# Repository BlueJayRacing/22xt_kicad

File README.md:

# 22xt_kicad, JHU Blue Jay Racing Repository
This is the KiCad Repository for the JHU 22XT DAQ Sub-team.

## Installation and User Guide
GitHub & KiCad Guide: https://docs.google.com/document/d/1nFm-e38JEY4i58-0UFxqdLA5TKqWCrV3EDKR8jGpRfA/edit?usp=sharing 

As a summary, you should be using **KiCad Version 9.0**. All project will be modular, and you should be storing all your step files, symbols, & footprints within the created folders.

Schematic settings & layout settings are described in the guide, as well as component derating.

## Branch Guide
You should be working on a new branch for each revision of your board. It is only when your board gets ordered on JLC that it should be merged with the main branch.

<ins>Branch naming structure:</ins> [0X]-[boardname]

Example:
> 01-main_board

<ins>How-To Create a Branch:</ins>

```
git checkout -b [your_branch] main
git push -u origin [your_branch]
```

## KiCad Project Name

Create your KiCad project on YOUR branch, within your current project folder.

<ins>Project filepath:</ins> [your_folder]/[boardname]_v[X]

Example Path:
> 01-main_board/main_board_v1

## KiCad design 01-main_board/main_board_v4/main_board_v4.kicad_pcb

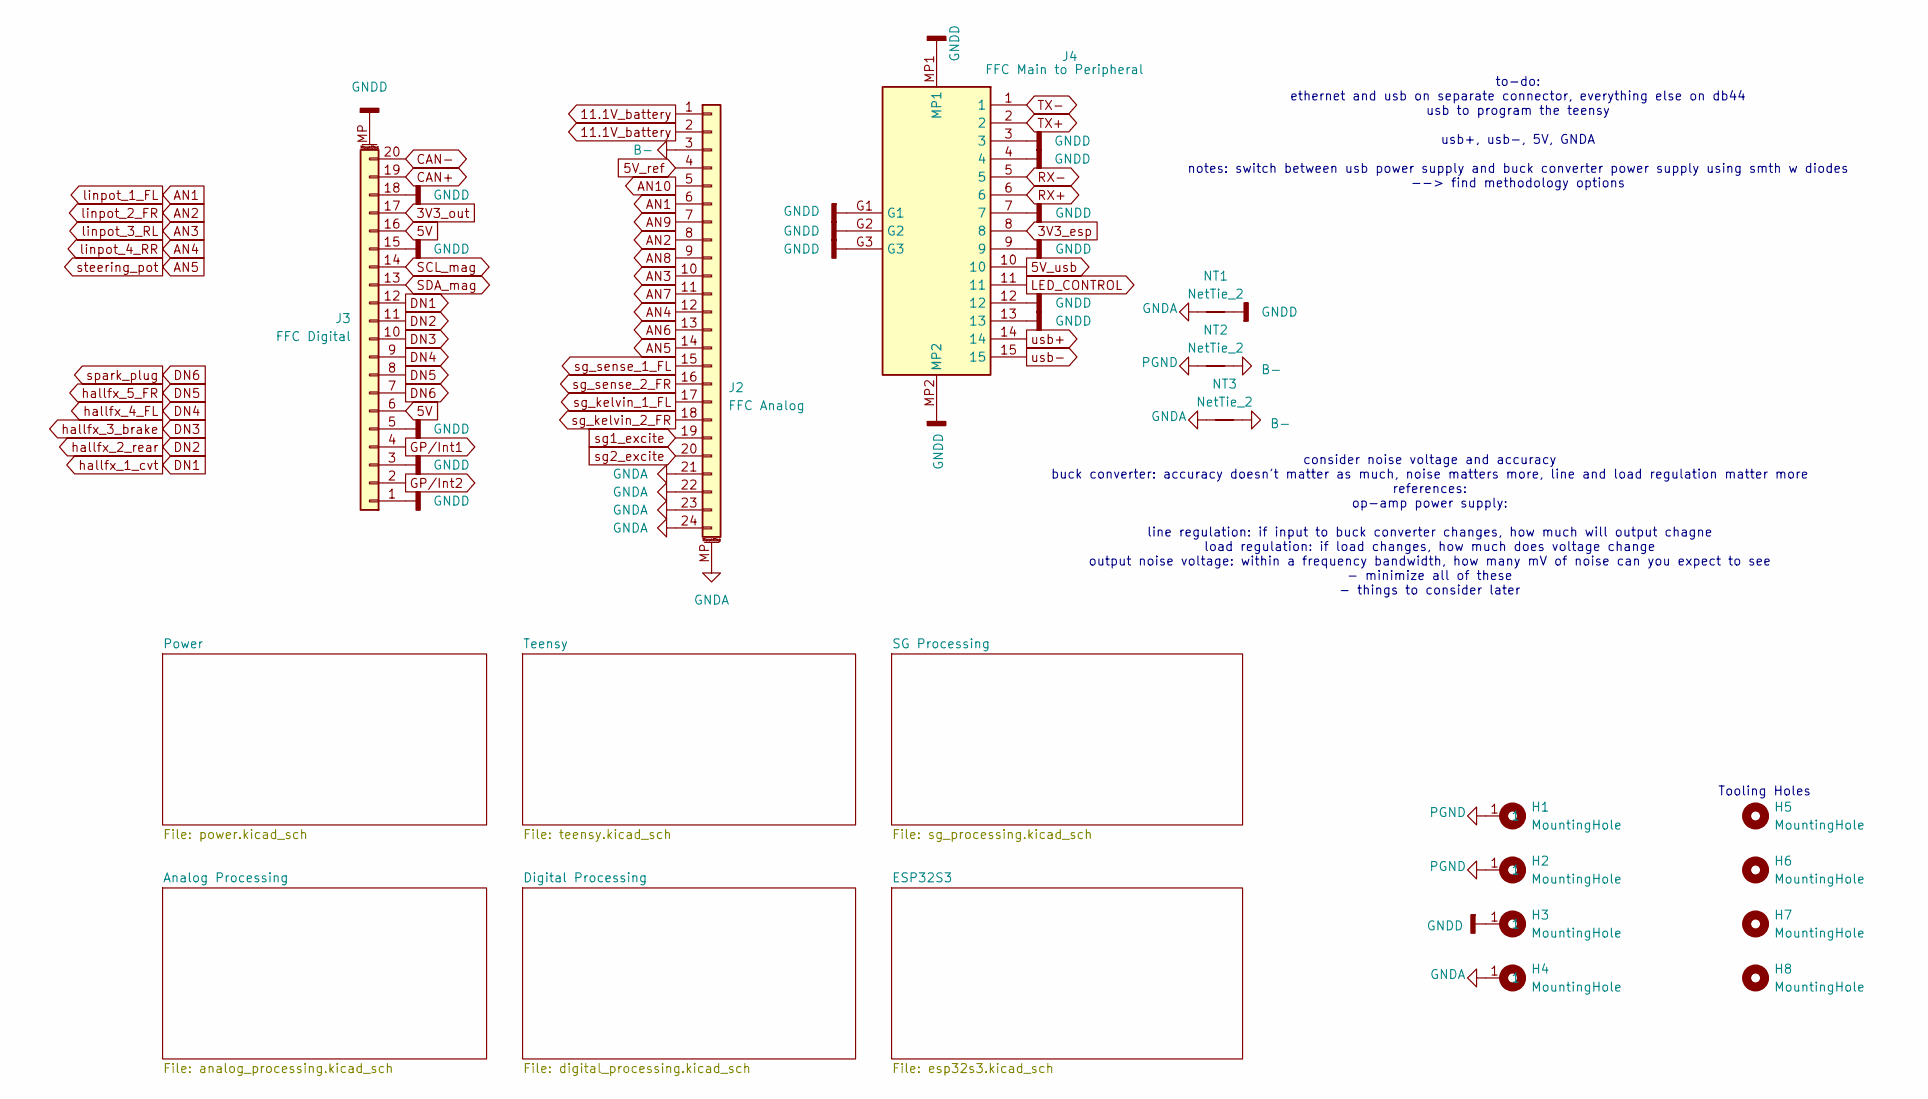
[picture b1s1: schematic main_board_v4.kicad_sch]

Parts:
H1, H2, H3, H4: MountingHole; MountingHole_2.5mm_Pad
H5, H6, H7, H8: MountingHole; ToolingHole_1.152mm
J2: FFC Analog; TE_2-84952-4_1x24-1MP_P1.0mm_Horizontal
J3: FFC Digital; TE_2-84952-0_1x20-1MP_P1.0mm_Horizontal
J4: FFC Main to Peripheral; FH4115S05SH05; Mouser Part Number 798-FH4115S05SH05
NT1, NT2, NT3: NetTie_2; NetTie-2_SMD_Pad0.5mm

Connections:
2V5: J2.19, J2.20; also elsewhere on the board
3V3_esp: J4.8; also elsewhere on the board
3V3_out: J3.17; also elsewhere on the board
5V: J3.6, J3.16; also elsewhere on the board
5V_ref: J2.4; also elsewhere on the board
5V_usb: J4.10; also elsewhere on the board
11.1V_battery: J2.1, J2.2; also elsewhere on the board
AN1: J2.6; also elsewhere on the board
AN2: J2.8; also elsewhere on the board
AN3: J2.10; also elsewhere on the board
AN4: J2.12; also elsewhere on the board
AN5: J2.14; also elsewhere on the board
AN6: J2.13; also elsewhere on the board
AN7: J2.11; also elsewhere on the board
AN8: J2.9; also elsewhere on the board
AN9: J2.7; also elsewhere on the board
AN10: J2.5; also elsewhere on the board
B-: J2.3, NT2.2, NT3.2
CAN+: J3.19; also elsewhere on the board
CAN-: J3.20; also elsewhere on the board
DN1: J3.12; also elsewhere on the board
DN2: J3.11; also elsewhere on the board
DN3: J3.10; also elsewhere on the board
DN4: J3.9; also elsewhere on the board
DN5: J3.8; also elsewhere on the board
DN6: J3.7; also elsewhere on the board
GNDA: H4.1, J2.21, J2.22, J2.23, J2.24, J2.MP (MountPin), NT1.1, NT3.1; also elsewhere on the board
GNDD: H3.1, J3.1, J3.3, J3.5, J3.15, J3.18, J3.MP (MountPin), J4.3, J4.4, J4.7, J4.9, J4.12, J4.13, J4.G1, J4.G2, J4.G3, J4.MP1, J4.MP2, NT1.2; also elsewhere on the board
GP/Int1: J3.4; also elsewhere on the board
GP/Int2: J3.2; also elsewhere on the board
LED_CONTROL: J4.11; also elsewhere on the board
PGND: H1.1, H2.1, NT2.1; also elsewhere on the board
RX+: J4.6; also elsewhere on the board
RX-: J4.5; also elsewhere on the board
SCL_mag: J3.14; also elsewhere on the board
SDA_mag: J3.13; also elsewhere on the board
TX+: J4.2; also elsewhere on the board
TX-: J4.1; also elsewhere on the board
sg1+: J2.17; also elsewhere on the board
sg2+: J2.18; also elsewhere on the board
sg_sense_1_FL: J2.15; also elsewhere on the board
sg_sense_2_FR: J2.16; also elsewhere on the board
usb+: J4.14; also elsewhere on the board
usb-: J4.15; also elsewhere on the board

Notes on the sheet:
consider noise voltage and accuracy buck converter: accuracy doesn't matter as much, noise matters more, line and load regulation matter more references: op-amp power supply: line regulation: if input to buck converter changes, how much will output chagne load regulation: if load changes, how much 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
to-do: ethernet and usb on separate connector, everything else on db44 usb to program the teensy usb+, usb-, 5V, GNDA notes: switch between usb power supply and buck converter power supply using smth w diodes --> find methodology options
Tooling Holes

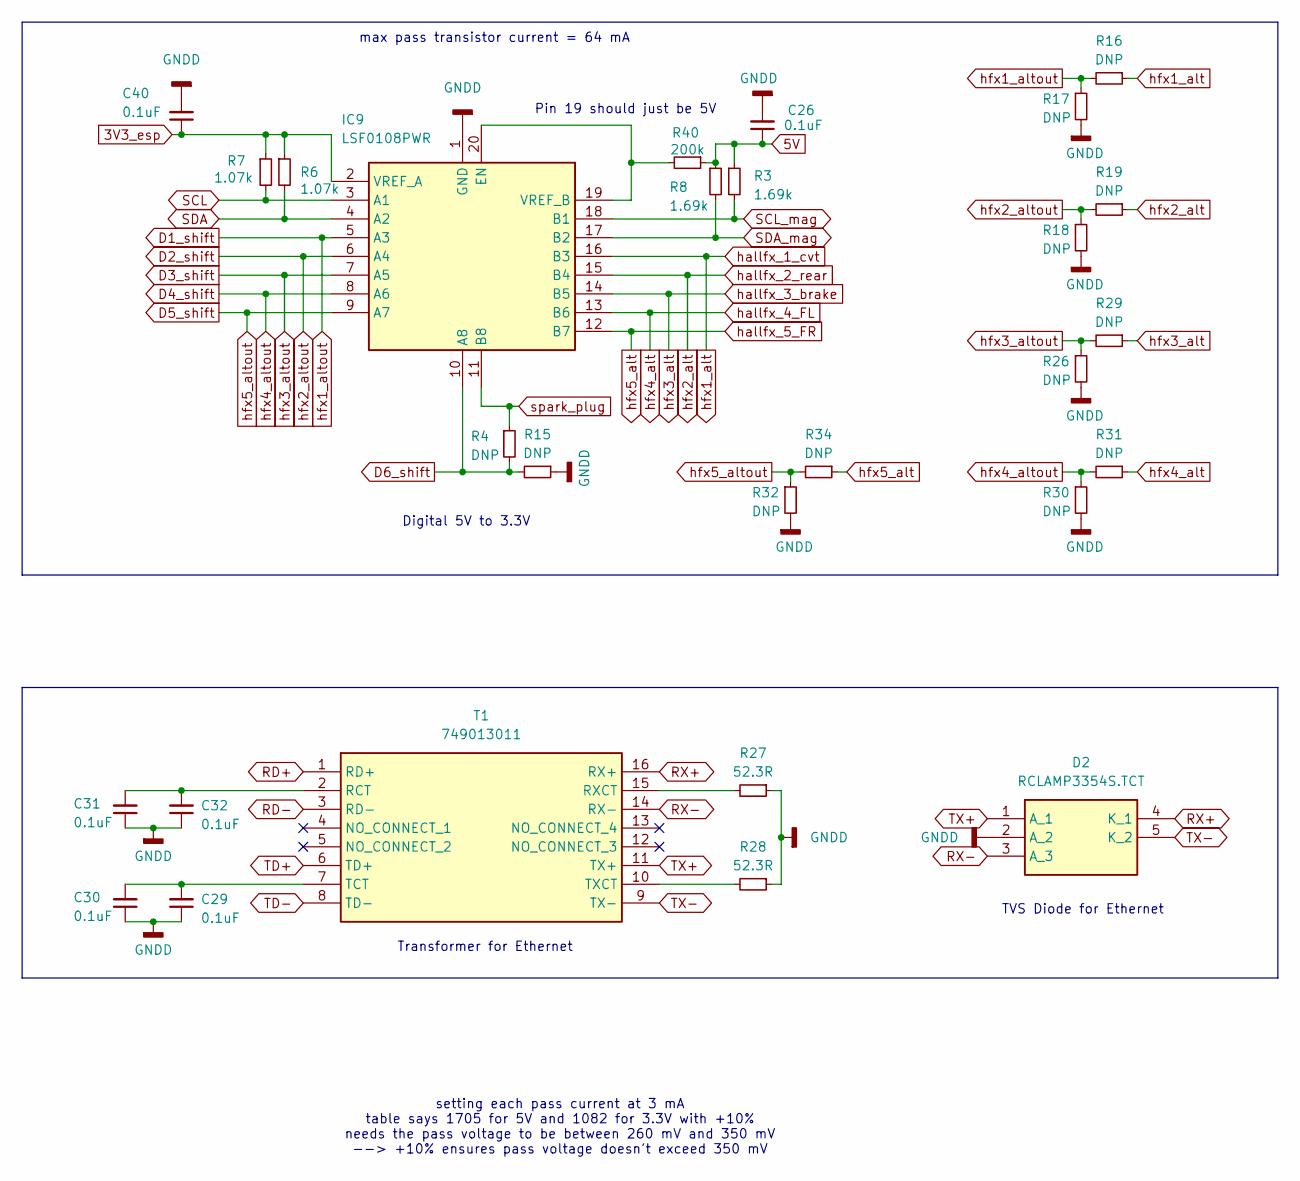
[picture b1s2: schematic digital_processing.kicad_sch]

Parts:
C26, C29, C30, C31, C32, C40: 0.1uF; C_0402_1005Metric
D2: RCLAMP3354S.TCT; SOT-23-5; Mouser Part Number 947-RCLAMP3354S.TCT
IC9: LSF0108PWR; SOP65P640X120-20N; Mouser Part Number 595-LSF0108RKSR
R3, R8: 1.69k; R_0402_1005Metric
R4, R15, R16, R17, R18, R19, R26, R29, R30, R31, R32, R34: DNP; R_0402_1005Metric
R6, R7: 1.07k; R_0402_1005Metric
R27, R28: 52.3R; R_0402_1005Metric
R40: 200k; R_0402_1005Metric
T1: 749013011; Mouser Part Number 710-749013011

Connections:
3V3_esp: C40.1, IC9.2 (VREF_A), R6.1, R7.1; also elsewhere on the board
5V: C26.1, R3.1, R8.1, R40.1; also elsewhere on the board
D1_shift: IC9.5 (A3), R16.2, R17.1; also elsewhere on the board
D2_shift: IC9.6 (A4), R18.1, R19.2; also elsewhere on the board
D3_shift: IC9.7 (A5), R26.1, R29.2; also elsewhere on the board
D4_shift: IC9.8 (A6), R30.1, R31.2; also elsewhere on the board
D5_shift: IC9.9 (A7), R32.1, R34.2; also elsewhere on the board
D6_shift: IC9.10 (A8), R4.2, R15.2; also elsewhere on the board
DN1: IC9.16 (B3), R16.1; also elsewhere on the board
DN2: IC9.15 (B4), R19.1; also elsewhere on the board
DN3: IC9.14 (B5), R29.1; also elsewhere on the board
DN4: IC9.13 (B6), R31.1; also elsewhere on the board
DN5: IC9.12 (B7), R34.1; also elsewhere on the board
DN6: IC9.11 (B8), R4.1; also elsewhere on the board
GNDD: C26.2, C29.1, C30.1, C31.1, C32.1, C40.2, D2.2 (A_2), IC9.1 (GND), R15.1, R17.2, R18.2, R26.2, R27.1, R28.1, R30.2, R32.2; also elsewhere on the board
unnamed: IC9.19 (VREF_B), IC9.20 (EN), R40.2
unnamed: C31.2, C32.2, T1.2 (RCT)
unnamed: R27.2, T1.15 (RXCT)
unnamed: C29.2, C30.2, T1.7 (TCT)
unnamed: R28.2, T1.10 (TXCT)
RD+: T1.1 (RD+); also elsewhere on the board
RD-: T1.3 (RD-); also elsewhere on the board
RX+: D2.4 (K_1), T1.16 (RX+); also elsewhere on the board
RX-: D2.3 (A_3), T1.14 (RX-); also elsewhere on the board
SCL: IC9.3 (A1), R7.2; also elsewhere on the board
SCL_mag: IC9.18 (B1), R3.2; also elsewhere on the board
SDA: IC9.4 (A2), R6.2; also elsewhere on the board
SDA_mag: IC9.17 (B2), R8.2; also elsewhere on the board
TD+: T1.6 (TD+); also elsewhere on the board
TD-: T1.8 (TD-); also elsewhere on the board
TX+: D2.1 (A_1), T1.11 (TX+); also elsewhere on the board
TX-: D2.5 (K_2), T1.9 (TX-); also elsewhere on the board

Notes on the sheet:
Transformer for Ethernet
max pass transistor current = 64 mA
Digital 5V to 3.3V
TVS Diode for Ethernet
setting each pass current at 3 mA table says 1705 for 5V and 1082 for 3.3V with +10% needs the pass voltage to be between 260 mV and 350 mV --> +10% ensures pass voltage doesn't exceed 350 mV
Pin 19 should just be 5V

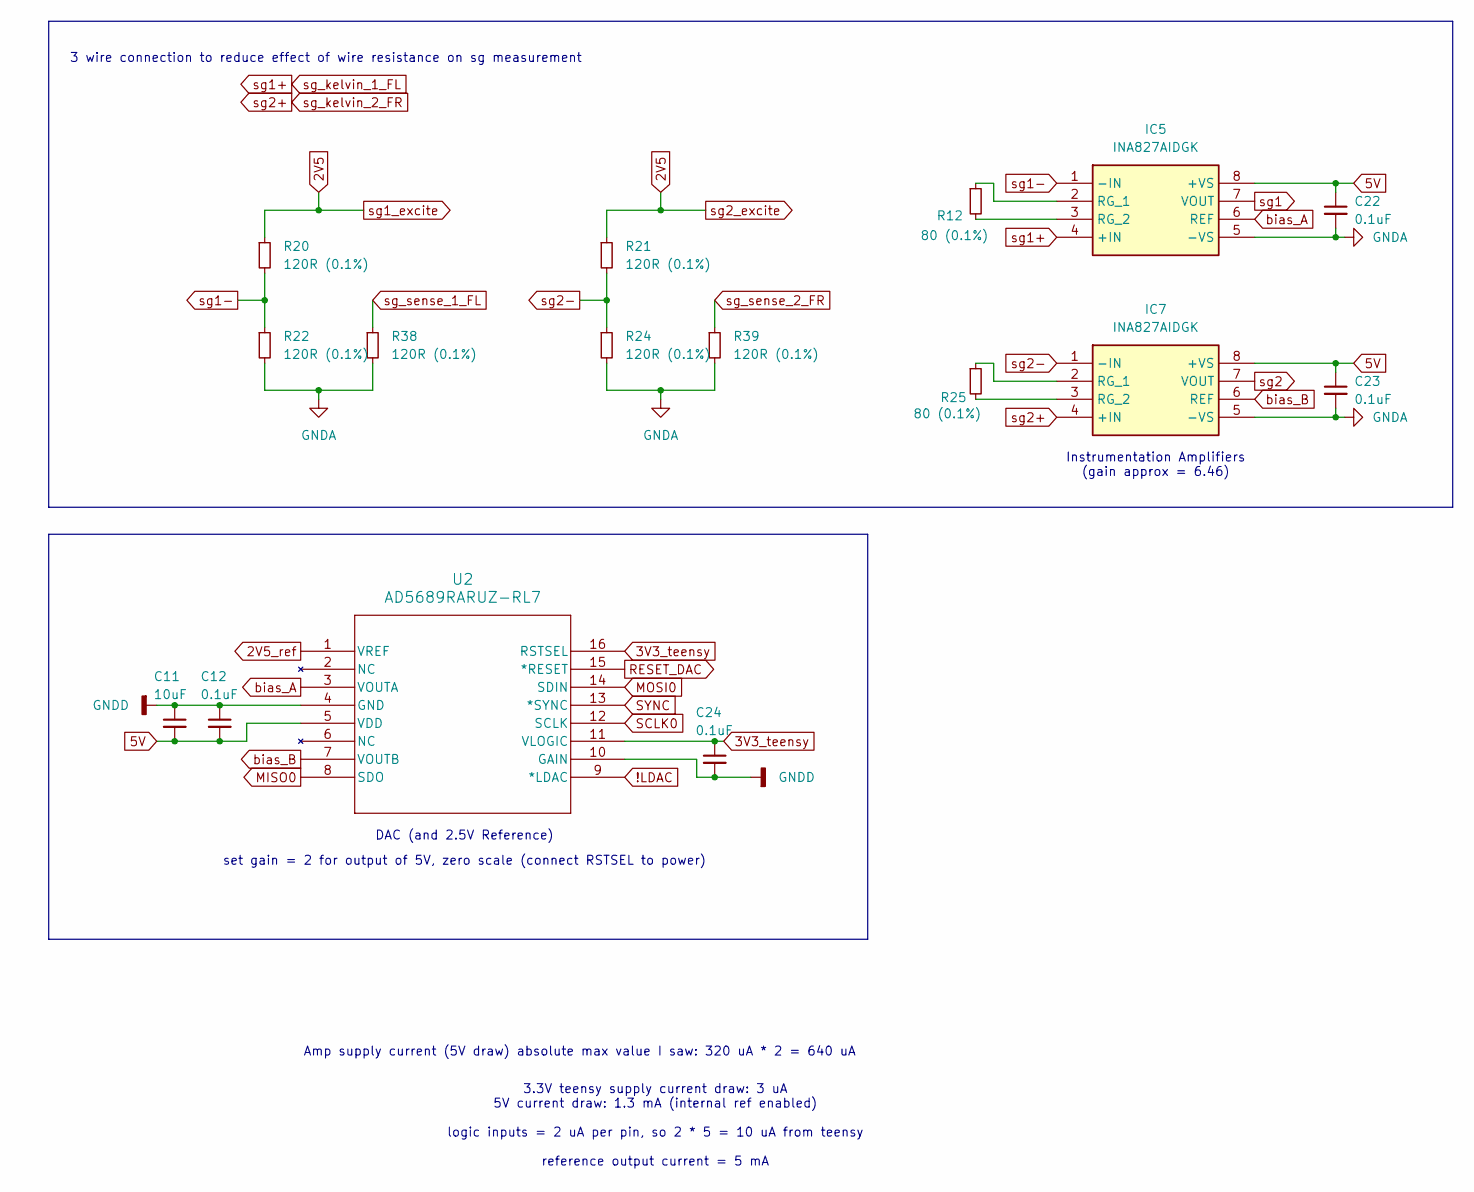
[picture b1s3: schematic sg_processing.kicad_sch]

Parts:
C11: 10uF; C_0603_1608Metric
C12, C22, C23, C24: 0.1uF; C_0402_1005Metric
IC5, IC7: INA827AIDGK; SOP65P490X110-8N; Mouser Part Number 595-INA827AIDGK
R12, R25: 80 (0.1%); R_0402_1005Metric
R20, R21, R22, R24, R38, R39: 120R (0.1%); R_0402_1005Metric
U2: AD5689RARUZ-RL7; RU_16_ADI

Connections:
2V5: R20.1, R21.1; also elsewhere on the board
2V5_ref: U2.1 (VREF); also elsewhere on the board
3V3_teensy: C24.1, U2.11 (VLOGIC), U2.16 (RSTSEL); also elsewhere on the board
5V: C11.2, C12.2, C22.1, C23.1, IC5.8 (+VS), IC7.8 (+VS), U2.5 (VDD); also elsewhere on the board
!LDAC: U2.9 (*LDAC); also elsewhere on the board
GNDA: C22.2, C23.2, IC5.5 (-VS), IC7.5 (-VS), R22.2, R24.2, R38.2, R39.2; also elsewhere on the board
GNDD: C11.1, C12.1, C24.2, U2.4 (GND), U2.10 (GAIN); also elsewhere on the board
MISO0: U2.8 (SDO); also elsewhere on the board
MOSI0: U2.14 (SDIN); also elsewhere on the board
unnamed: IC5.2 (RG_1), R12.1
unnamed: IC5.3 (RG_2), R12.2
unnamed: IC7.2 (RG_1), R25.1
unnamed: IC7.3 (RG_2), R25.2
RESET_DAC: U2.15 (*RESET); also elsewhere on the board
SCLK0: U2.12 (SCLK); also elsewhere on the board
SYNC: U2.13 (*SYNC); also elsewhere on the board
bias_A: IC5.6 (REF), U2.3 (VOUTA)
bias_B: IC7.6 (REF), U2.7 (VOUTB)
sg1: IC5.7 (VOUT); also elsewhere on the board
sg1+: IC5.4 (+IN); also elsewhere on the board
sg1-: IC5.1 (-IN), R20.2, R22.1
sg2: IC7.7 (VOUT); also elsewhere on the board
sg2+: IC7.4 (+IN); also elsewhere on the board
sg2-: IC7.1 (-IN), R21.2, R24.1
sg_sense_1_FL: R38.1; also elsewhere on the board
sg_sense_2_FR: R39.1; also elsewhere on the board

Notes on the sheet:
DAC (and 2.5V Reference)
Amp supply current (5V draw) absolute max value I saw: 320 uA * 2 = 640 uA
3.3V teensy supply current draw: 3 uA 5V current draw: 1.3 mA (internal ref enabled) logic inputs = 2 uA per pin, so 2 * 5 = 10 uA from teensy reference output current = 5 mA
set gain = 2 for output of 5V, zero scale (connect RSTSEL to power)
Instrumentation Amplifiers (gain approx = 6.46)
3 wire connection to reduce effect of wire resistance on sg measurement

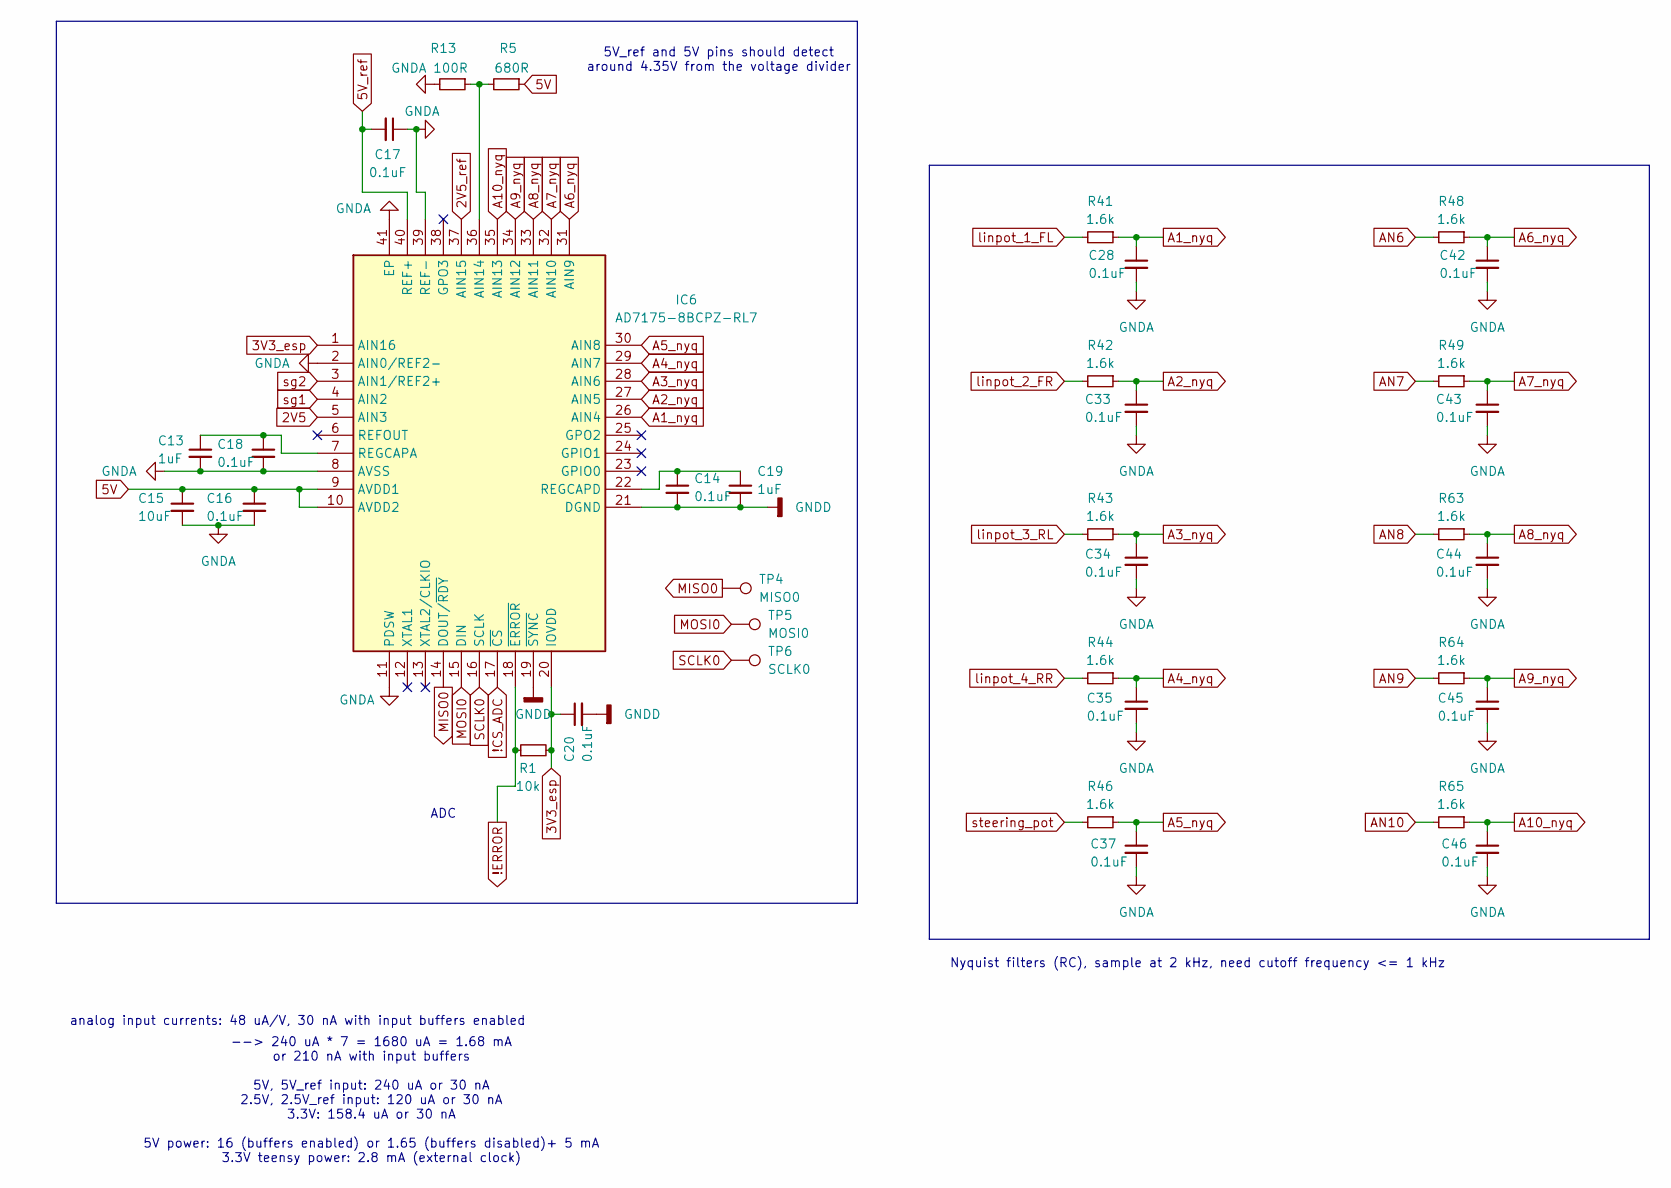
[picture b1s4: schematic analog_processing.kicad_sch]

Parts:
C13, C19: 1uF; C_0402_1005Metric
C14, C16, C17, C18, C20, C28, C33, C34, C35, C37, C42, C43, C44, C45, C46: 0.1uF; C_0402_1005Metric
C15: 10uF; C_0603_1608Metric
IC6: AD7175-8BCPZ-RL7; QFN50P600X600X80-41N-D; Mouser Part Number 584-AD7175-8BCPZ-RL7
R1: 10k; R_0402_1005Metric
R5: 680R; R_0402_1005Metric
R13: 100R; R_0402_1005Metric
R41, R42, R43, R44, R46, R48, R49, R63, R64, R65: 1.6k; R_0402_1005Metric
TP4: MISO0; TestPoint_Pad_1.0x1.0mm
TP5: MOSI0; TestPoint_Pad_1.0x1.0mm
TP6: SCLK0; TestPoint_Pad_1.0x1.0mm

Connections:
2V5: IC6.5 (AIN3); also elsewhere on the board
2V5_ref: IC6.37 (AIN15); also elsewhere on the board
3V3_esp: C20.1, IC6.1 (AIN16), IC6.20 (IOVDD), R1.2; also elsewhere on the board
5V: C15.1, C16.1, IC6.9 (AVDD1), IC6.10 (AVDD2), R5.1; also elsewhere on the board
5V_ref: C17.2, IC6.40 (REF+); also elsewhere on the board
!CS_ADC: IC6.17 (~CS); also elsewhere on the board
!ERROR: IC6.18 (~ERROR), R1.1; also elsewhere on the board
A1_nyq: C28.1, IC6.26 (AIN4), R41.1
A2_nyq: C33.1, IC6.27 (AIN5), R42.1
A3_nyq: C34.1, IC6.28 (AIN6), R43.1
A4_nyq: C35.1, IC6.29 (AIN7), R44.1
A5_nyq: C37.1, IC6.30 (AIN8), R46.1
A6_nyq: C42.1, IC6.31 (AIN9), R48.1
A7_nyq: C43.1, IC6.32 (AIN10), R49.1
A8_nyq: C44.1, IC6.33 (AIN11), R63.1
A9_nyq: C45.1, IC6.34 (AIN12), R64.1
A10_nyq: C46.1, IC6.35 (AIN13), R65.1
AN1: R41.2; also elsewhere on the board
AN2: R42.2; also elsewhere on the board
AN3: R43.2; also elsewhere on the board
AN4: R44.2; also elsewhere on the board
AN5: R46.2; also elsewhere on the board
AN6: R48.2; also elsewhere on the board
AN7: R49.2; also elsewhere on the board
AN8: R63.2; also elsewhere on the board
AN9: R64.2; also elsewhere on the board
AN10: R65.2; also elsewhere on the board
GNDA: C13.2, C15.2, C16.2, C17.1, C18.2, C28.2, C33.2, C34.2, C35.2, C37.2, C42.2, C43.2, C44.2, C45.2, C46.2, IC6.2 (AIN0/REF2-), IC6.8 (AVSS), IC6.11 (PDSW), IC6.39 (REF-), IC6.41 (EP), R13.2; also elsewhere on the board
GNDD: C14.2, C19.2, C20.2, IC6.19 (~SYNC), IC6.21 (DGND); also elsewhere on the board
MISO0: IC6.14 (DOUT/~RDY), TP4.1; also elsewhere on the board
MOSI0: IC6.15 (DIN), TP5.1; also elsewhere on the board
unnamed: IC6.36 (AIN14), R5.2, R13.1
unnamed: C13.1, C18.1, IC6.7 (REGCAPA)
unnamed: C14.1, C19.1, IC6.22 (REGCAPD)
SCLK0: IC6.16 (SCLK), TP6.1; also elsewhere on the board
sg1: IC6.4 (AIN2); also elsewhere on the board
sg2: IC6.3 (AIN1/REF2+); also elsewhere on the board

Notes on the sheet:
ADC
--> 240 uA * 7 = 1680 uA = 1.68 mA or 210 nA with input buffers 5V, 5V_ref input: 240 uA or 30 nA 2.5V, 2.5V_ref input: 120 uA or 30 nA 3.3V: 158.4 uA or 30 nA 5V power: 16 (buffers enabled) or 1.65 (buffers disabled)+ 5 mA 3.3V teensy power: 2.8 mA (external clock)
analog input currents: 48 uA/V, 30 nA with input buffers enabled
Nyquist filters (RC), sample at 2 kHz, need cutoff frequency <= 1 kHz
5V_ref and 5V pins should detect around 4.35V from the voltage divider

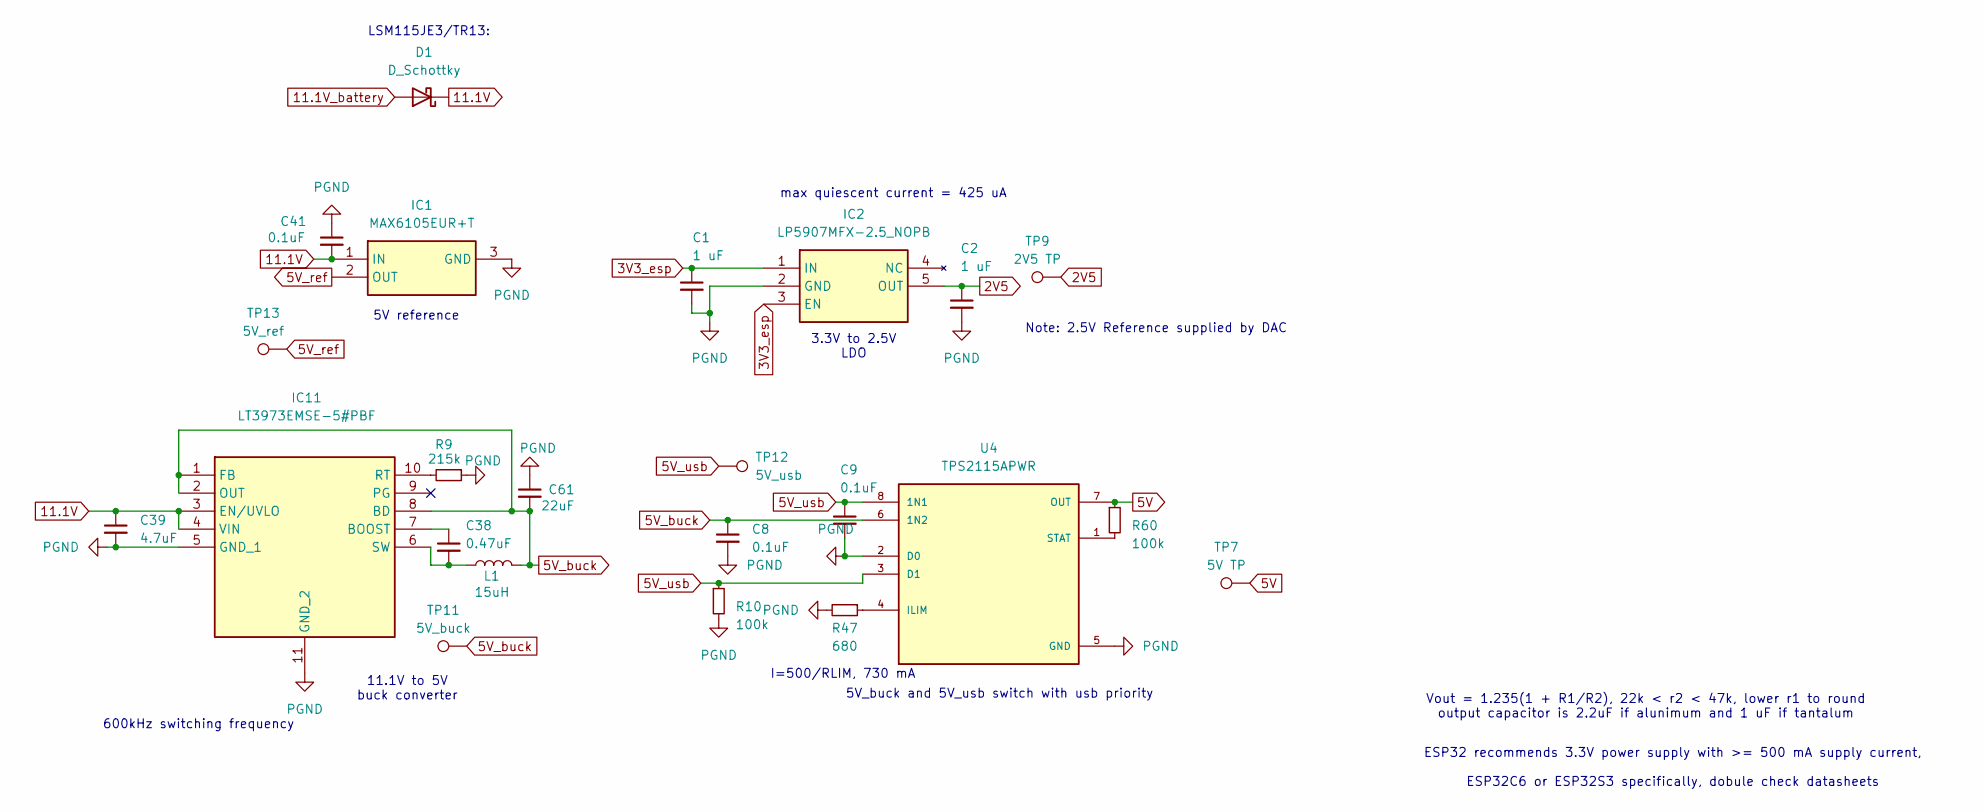
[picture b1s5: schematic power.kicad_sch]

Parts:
C1, C2: 1 uF; C_0402_1005Metric
C8, C9, C41: 0.1uF; C_0402_1005Metric
C38: 0.47uF; C_0402_1005Metric
C39: 4.7uF; C_0402_1005Metric
C61: 22uF; C_0603_1608Metric
D1: D_Schottky; DO-214BA_MCH
IC1: MAX6105EUR+T; SOT-23-3; Mouser Part Number 700-MAX6105EURT
IC2: LP5907MFX-2.5_NOPB; SOT-23-5; Mouser Part Number 595-LP5907MFX2.5NOPB
IC11: LT3973EMSE-5#PBF; Mouser Part Number 584-LT3973EMSE-5#PBF
L1: 15uH; NRS4012T150MDGJ
R9: 215k; R_0402_1005Metric
R10, R60: 100k; R_0402_1005Metric
R47: 680; R_0402_1005Metric
TP7: 5V TP; TestPoint_Pad_1.0x1.0mm
TP9: 2V5 TP; TestPoint_Pad_1.0x1.0mm
TP11: 5V_buck; TestPoint_Pad_1.0x1.0mm
TP12: 5V_usb; TestPoint_Pad_1.0x1.0mm
TP13: 5V_ref; TestPoint_Pad_1.0x1.0mm
U4: TPS2115APWR; SOP65P640X120-8N; PARTREV F

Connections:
2V5: C2.1, IC2.5 (OUT), TP9.1; also elsewhere on the board
3V3_esp: C1.1, IC2.1 (IN), IC2.3 (EN); also elsewhere on the board
5V: R60.1, TP7.1, U4.7 (OUT); also elsewhere on the board
5V_buck: C8.1, C61.2, IC11.1 (FB), IC11.2 (OUT), IC11.8 (BD), L1.2, TP11.1, U4.6 (1N2)
5V_ref: IC1.2 (OUT), TP13.1; also elsewhere on the board
5V_usb: C9.1, R10.1, TP12.1, U4.3 (D1), U4.8 (1N1); also elsewhere on the board
11.1V: C39.1, C41.2, D1.1 (K), IC1.1 (IN), IC11.3 (EN/UVLO), IC11.4 (VIN)
11.1V_battery: D1.2 (A); also elsewhere on the board
unnamed: C38.1, IC11.7 (BOOST)
unnamed: IC11.10 (RT), R9.2
unnamed: C38.2, IC11.6 (SW), L1.1
unnamed: R47.1, U4.4 (ILIM)
unnamed: R60.2, U4.1 (STAT)
PGND: C1.2, C2.2, C8.2, C9.2, C39.2, C41.1, C61.1, IC1.3 (GND), IC2.2 (GND), IC11.5 (GND_1), IC11.11 (GND_2), R9.1, R10.2, R47.2, U4.2 (D0), U4.5 (GND); also elsewhere on the board

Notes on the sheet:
5V reference
LSM115JE3/TR13:
11.1V to 5V buck converter
5V_buck and 5V_usb switch with usb priority
max quiescent current = 425 uA
I=500/RLIM, 730 mA
ESP32 recommends 3.3V power supply with >= 500 mA supply current, ESP32C6 or ESP32S3 specifically, dobule check datasheets
Vout = 1.235(1 + R1/R2), 22k < r2 < 47k, lower r1 to round output capacitor is 2.2uF if alunimum and 1 uF if tantalum
3.3V to 2.5V LDO
Note: 2.5V Reference supplied by DAC
600kHz switching frequency

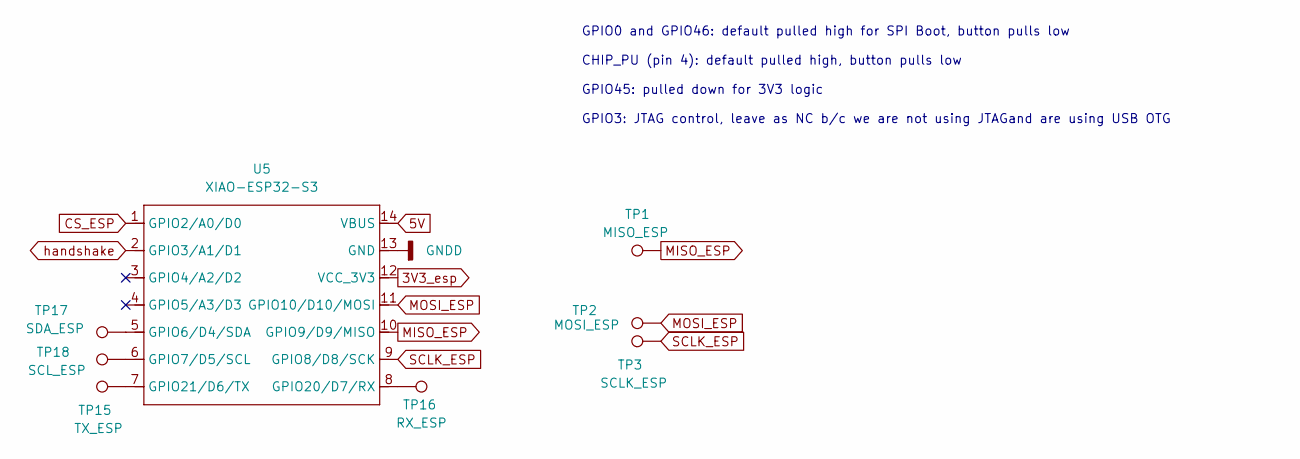
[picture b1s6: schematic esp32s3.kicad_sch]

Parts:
TP1: MISO_ESP; TestPoint_Pad_1.0x1.0mm
TP2: MOSI_ESP; TestPoint_Pad_1.0x1.0mm
TP3: SCLK_ESP; TestPoint_Pad_1.0x1.0mm
TP15: TX_ESP; TestPoint_Pad_1.0x1.0mm
TP16: RX_ESP; TestPoint_Pad_1.0x1.0mm
TP17: SDA_ESP; TestPoint_Pad_1.0x1.0mm
TP18: SCL_ESP; TestPoint_Pad_1.0x1.0mm
U5: XIAO-ESP32-S3; XIAO-ESP32S3-SMD

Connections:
3V3_esp: U5.12 (VCC_3V3); also elsewhere on the board
5V: U5.14 (VBUS); also elsewhere on the board
CS_ESP: U5.1 (GPIO2/A0/D0); also elsewhere on the board
GNDD: U5.13 (GND); also elsewhere on the board
MISO_ESP: TP1.1, U5.10 (GPIO9/D9/MISO); also elsewhere on the board
MOSI_ESP: TP2.1, U5.11 (GPIO10/D10/MOSI); also elsewhere on the board
unnamed: TP17.1, U5.5 (GPIO6/D4/SDA)
unnamed: TP18.1, U5.6 (GPIO7/D5/SCL)
unnamed: TP16.1, U5.8 (GPIO20/D7/RX)
unnamed: TP15.1, U5.7 (GPIO21/D6/TX)
SCLK_ESP: TP3.1, U5.9 (GPIO8/D8/SCK); also elsewhere on the board
handshake: U5.2 (GPIO3/A1/D1)

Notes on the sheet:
GPIO0 and GPIO46: default pulled high for SPI Boot, button pulls low CHIP_PU (pin 4): default pulled high, button pulls low GPIO45: pulled down for 3V3 logic GPIO3: JTAG control, leave as NC b/c we are not using JTAGand are using USB OTG

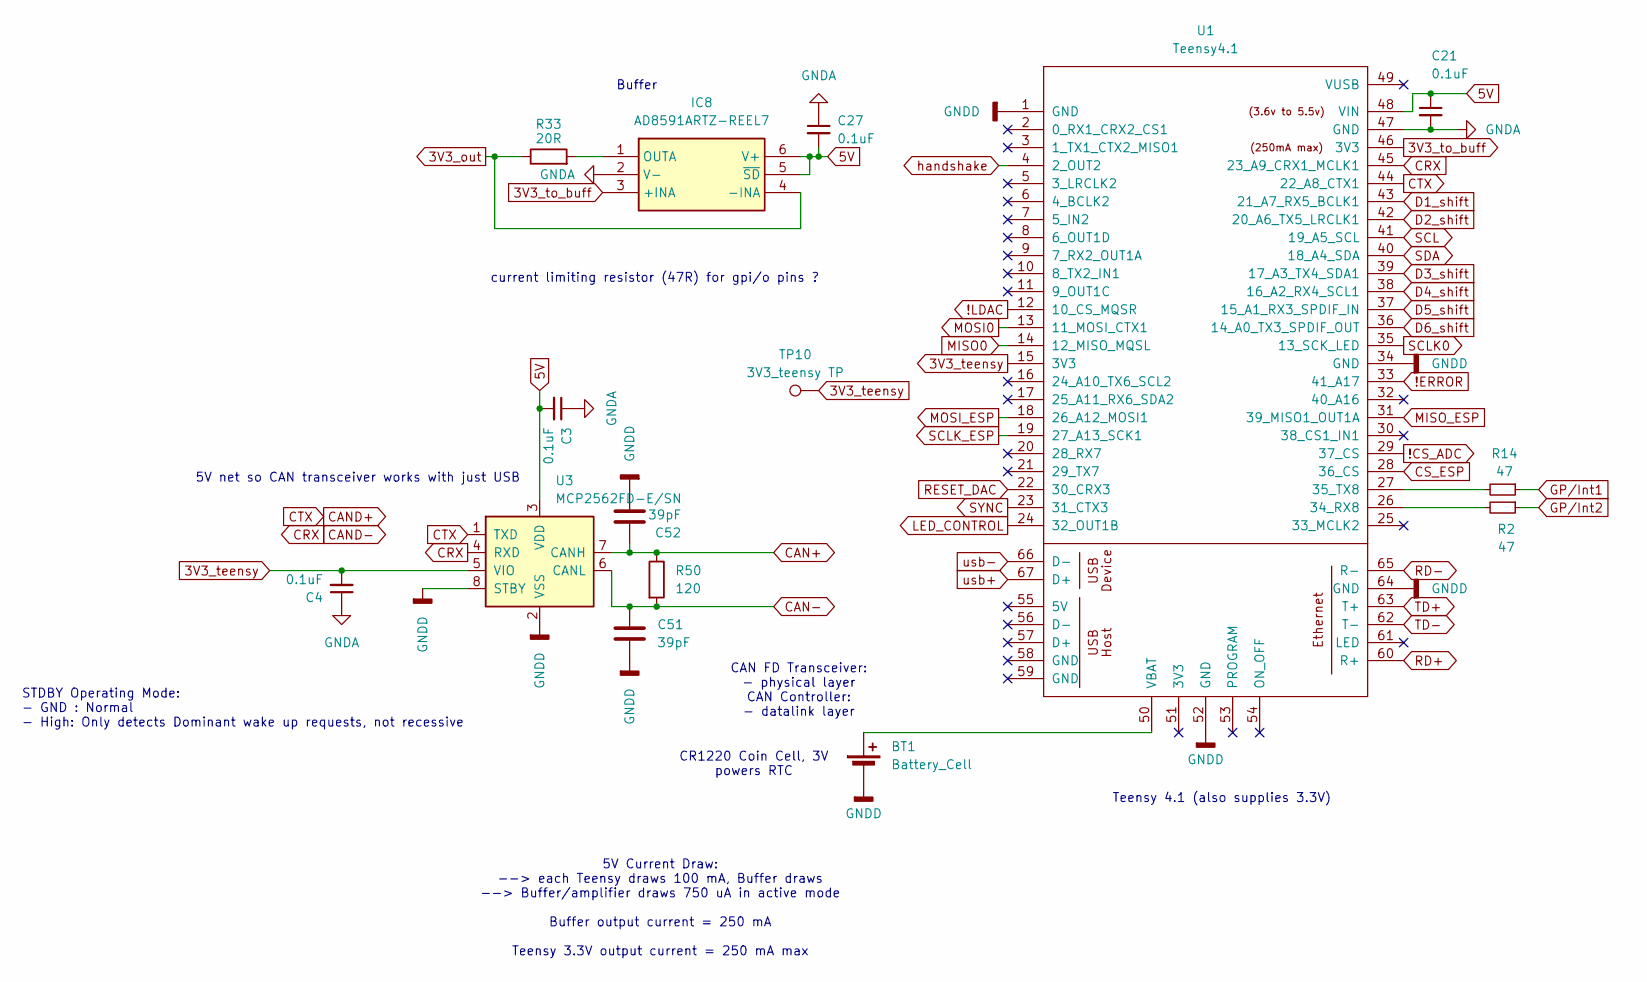
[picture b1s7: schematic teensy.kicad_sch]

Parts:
BT1: Battery_Cell; BatteryHolder_LINX_BAT-HLD-012-SMT
C3, C4, C21, C27: 0.1uF; C_0402_1005Metric
C51, C52: 39pF; C_0402_1005Metric
IC8: AD8591ARTZ-REEL7; SOT95P280X145-6N; Mouser Part Number 584-AD8591ARTZ-R7
R2, R14: 47; R_0402_1005Metric
R33: 20R; R_0402_1005Metric
R50: 120; R_1206_3216Metric
TP10: 3V3_teensy TP; TestPoint_Pad_1.0x1.0mm
U1: Teensy4.1; Teensy41
U3: MCP2562FD-E/SN; SOIC-8_3.9x4.9mm_P1.27mm

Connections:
3V3_out: IC8.4 (-INA), R33.1; also elsewhere on the board
3V3_teensy: C4.2, TP10.1, U1.15 (3V3), U3.5 (VIO); also elsewhere on the board
3V3_to_buff: IC8.3 (+INA), U1.46 (3V3)
5V: C3.2, C21.1, C27.2, IC8.5 (~SD), IC8.6 (V+), U1.48 (VIN), U3.3 (VDD); also elsewhere on the board
!CS_ADC: U1.29 (37_CS); also elsewhere on the board
!ERROR: U1.33 (41_A17); also elsewhere on the board
!LDAC: U1.12 (10_CS_MQSR); also elsewhere on the board
CAN+: C52.1, R50.1, U3.7 (CANH); also elsewhere on the board
CAN-: C51.1, R50.2, U3.6 (CANL); also elsewhere on the board
CAND+: U1.44 (22_A8_CTX1), U3.1 (TXD)
CAND-: U1.45 (23_A9_CRX1_MCLK1), U3.4 (RXD)
CS_ESP: U1.28 (36_CS); also elsewhere on the board
D1_shift: U1.43 (21_A7_RX5_BCLK1); also elsewhere on the board
D2_shift: U1.42 (20_A6_TX5_LRCLK1); also elsewhere on the board
D3_shift: U1.39 (17_A3_TX4_SDA1); also elsewhere on the board
D4_shift: U1.38 (16_A2_RX4_SCL1); also elsewhere on the board
D5_shift: U1.37 (15_A1_RX3_SPDIF_IN); also elsewhere on the board
D6_shift: U1.36 (14_A0_TX3_SPDIF_OUT); also elsewhere on the board
GNDA: C3.1, C4.1, C21.2, C27.1, IC8.2 (V-), U1.47 (GND); also elsewhere on the board
GNDD: BT1.2 (-), C51.2, C52.2, U1.1 (GND), U1.34 (GND), U1.52 (GND), U1.64 (GND), U3.2 (VSS), U3.8 (STBY); also elsewhere on the board
GP/Int1: R14.1; also elsewhere on the board
GP/Int2: R2.1; also elsewhere on the board
LED_CONTROL: U1.24 (32_OUT1B); also elsewhere on the board
MISO0: U1.14 (12_MISO_MQSL); also elsewhere on the board
MISO_ESP: U1.31 (39_MISO1_OUT1A); also elsewhere on the board
MOSI0: U1.13 (11_MOSI_CTX1); also elsewhere on the board
MOSI_ESP: U1.18 (26_A12_MOSI1); also elsewhere on the board
unnamed: BT1.1 (+), U1.50 (VBAT)
unnamed: IC8.1 (OUTA), R33.2
unnamed: R2.2, U1.26 (34_RX8)
unnamed: R14.2, U1.27 (35_TX8)
RD+: U1.60 (R+); also elsewhere on the board
RD-: U1.65 (R-); also elsewhere on the board
RESET_DAC: U1.22 (30_CRX3); also elsewhere on the board
SCL: U1.41 (19_A5_SCL); also elsewhere on the board
SCLK0: U1.35 (13_SCK_LED); also elsewhere on the board
SCLK_ESP: U1.19 (27_A13_SCK1); also elsewhere on the board
SDA: U1.40 (18_A4_SDA); also elsewhere on the board
SYNC: U1.23 (31_CTX3); also elsewhere on the board
TD+: U1.63 (T+); also elsewhere on the board
TD-: U1.62 (T-); also elsewhere on the board
usb+: U1.67 (D+); also elsewhere on the board
usb-: U1.66 (D-); also elsewhere on the board

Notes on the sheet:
Buffer
5V Current Draw: --> each Teensy draws 100 mA, Buffer draws --> Buffer/amplifier draws 750 uA in active mode Buffer output current = 250 mA Teensy 3.3V output current = 250 mA max
STDBY Operating Mode: - GND : Normal - High: Only detects Dominant wake up requests, not recessive
CR1220 Coin Cell, 3V powers RTC
Teensy 4.1 (also supplies 3.3V)
5V net so CAN transceiver works with just USB
CAN FD Transceiver: - physical layer CAN Controller: - datalink layer
current limiting resistor (47R) for gpi/o pins ?
